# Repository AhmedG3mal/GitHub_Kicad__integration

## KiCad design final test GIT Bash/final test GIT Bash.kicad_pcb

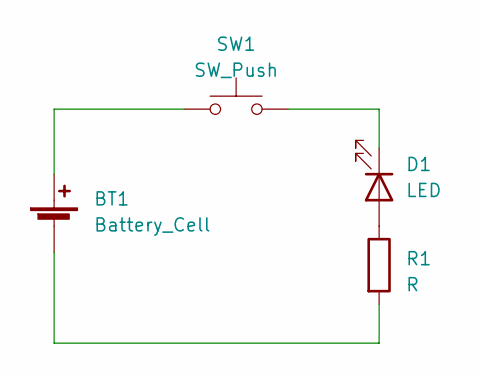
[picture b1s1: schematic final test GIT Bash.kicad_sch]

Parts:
BT1: Battery_Cell; BatteryHolder_Bulgin_BX0036_1xC
D1: LED; LED_D5.0mm_Clear
R1: R; R_Axial_DIN0414_L11.9mm_D4.5mm_P15.24mm_Horizontal
SW1: SW_Push; SW_PUSH-12mm

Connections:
unnamed: BT1.1 (+), SW1.1
unnamed: BT1.2 (-), R1.2
unnamed: D1.2 (A), R1.1
unnamed: D1.1 (K), SW1.2

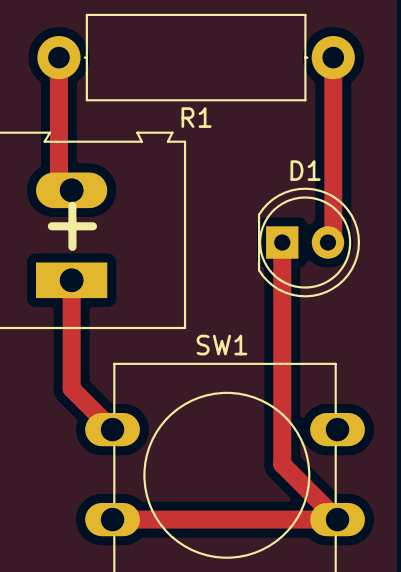
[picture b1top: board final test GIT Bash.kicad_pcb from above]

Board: 2 copper layers, 4 parts (0 on the bottom side), 4 nets.

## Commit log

2024-02-14 Intial commit
2024-02-14 THT Footprint assigned
